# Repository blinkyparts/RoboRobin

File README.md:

# Robo Robin

- A very simple kit for children aged 4 and over
- Plug-in components for easier soldering
- Circuit visible on the back for explanation
- Compatibility of hands with certain other toys of Danish design

- Status: **Complete**
- Difficulty: **1/5**

### Parts List

| Description                   | Quantity |
|-------------------------------|----------|
| RGB LEDs 5mm                  |     2    |
| Button (SMD)                  |     1    |
| CR2032 Battery Holder (THT)   |     1    |
| CR2032 Battery (not included) |     1    |

### Manual
You can find the manual and pictures of every step here: https://github.com/Binary-Kitchen/SolderingTutorial

### 3D Print
There is also a special clamp brick for Robo robin to use in your constructions and imagination.: https://www.printables.com/de/model/513639-klemmbaustein-brick-stand-for-the-robo-robin

### Copyright and Authorship

- Board: [CC-BY-NC-SA 4.0](https://creativecommons.org/licenses/by-nc-sa/4.0/) - [Timo from blinkyparts.com](https://shop.blinkyparts.com)
- Robot SVG [CC-BY-SA 3.0](https://creativecommons.org/licenses/by-sa/3.0/) - [Robot by iconcheese from thenounproject.com](https://thenounproject.com/icon/robot-1159392/) (We bought a licence, you should also honour the author.)

### Buy Soldering Kits
If you want to buy the parts and PCB for a soldering kit you can find everything here: [shop.blinkyparts.com](https://shop.blinkyparts.com/de/Robo-Robin-Loetbausatz-Der-sehr-einfache-lustig-rote-Roboterbausatz/blink239442)

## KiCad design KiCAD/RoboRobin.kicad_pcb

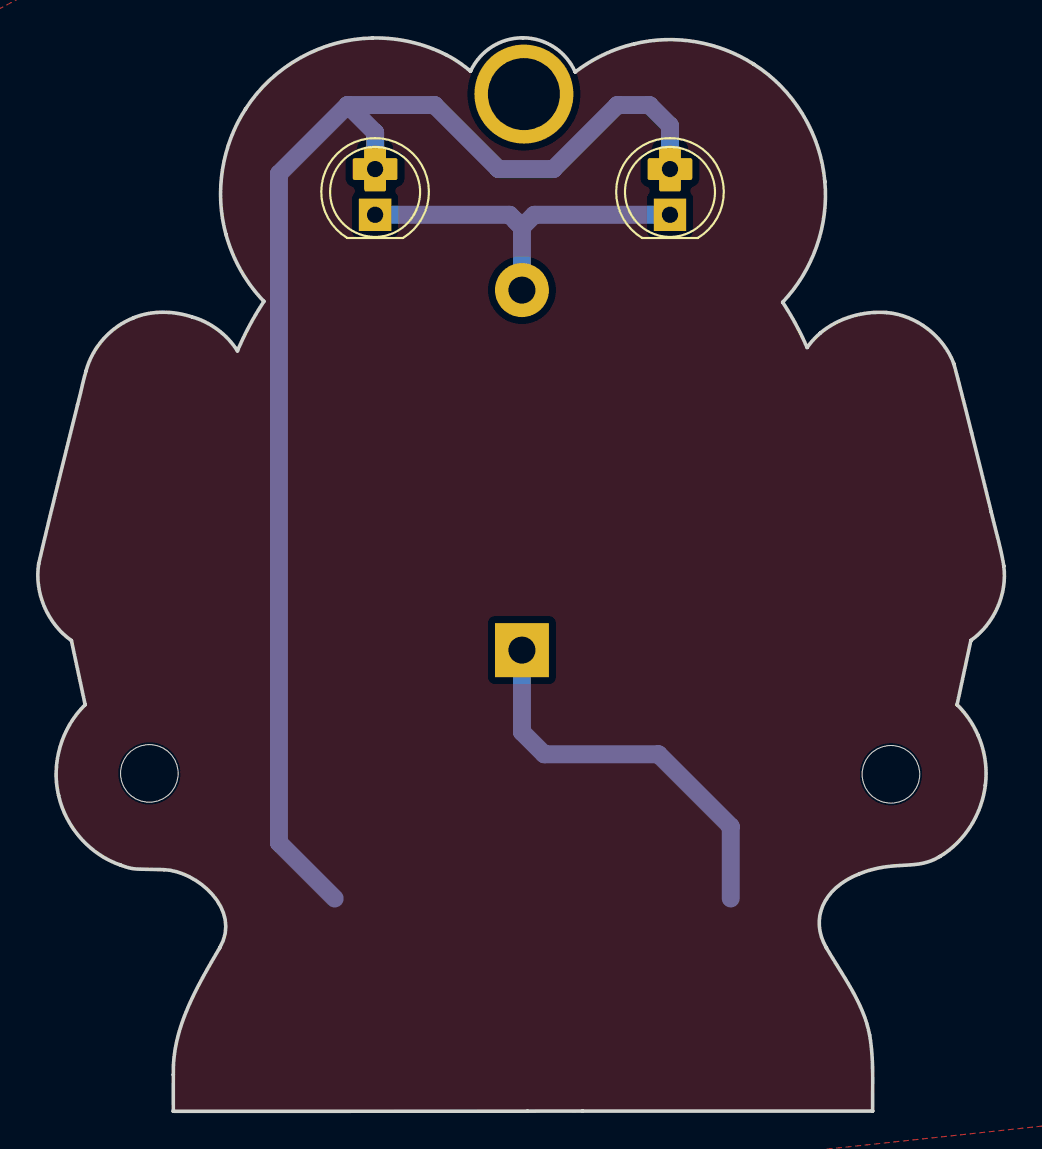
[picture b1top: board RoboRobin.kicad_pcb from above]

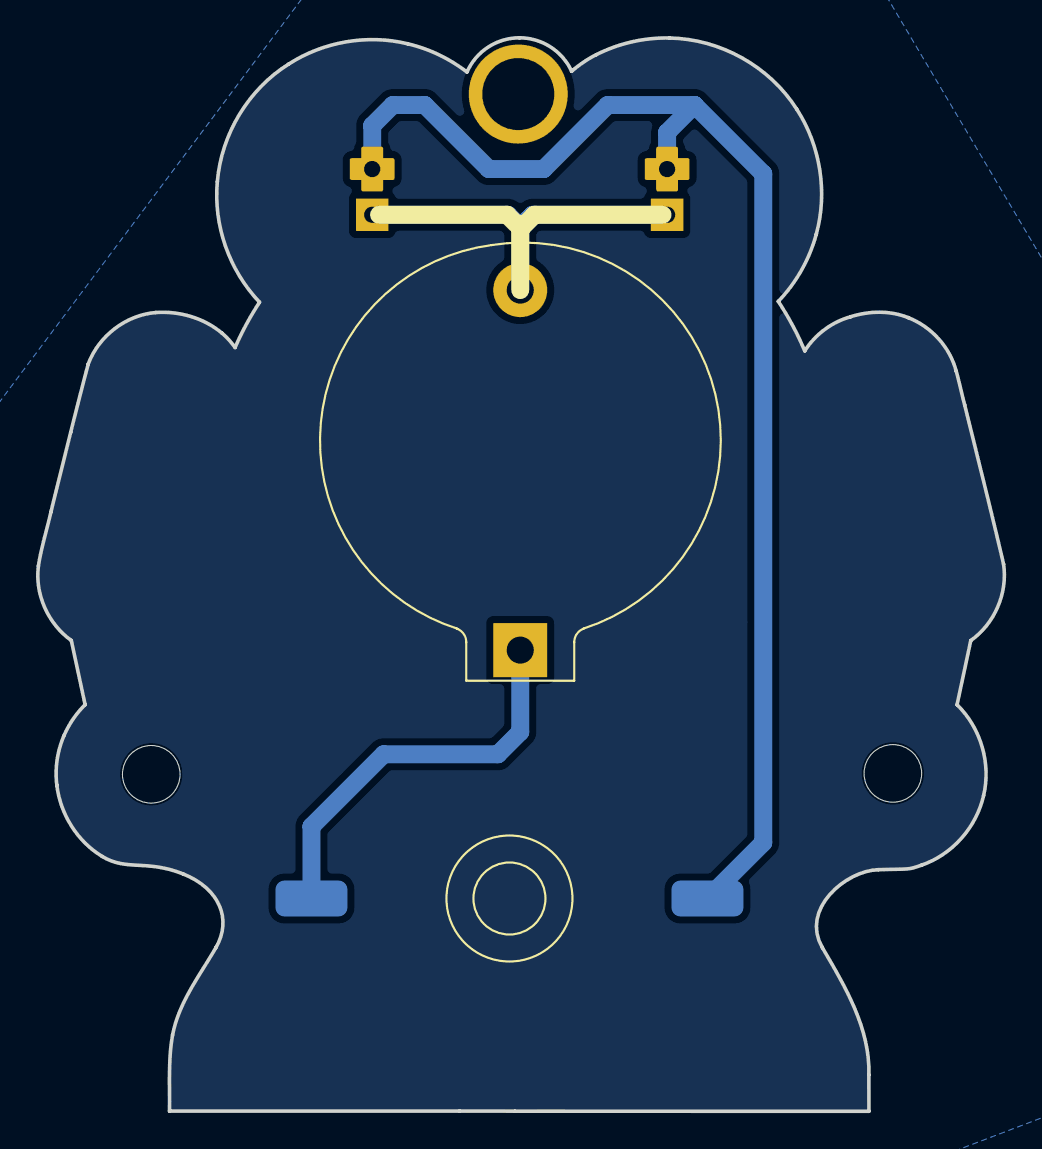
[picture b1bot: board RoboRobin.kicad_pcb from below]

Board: 2 copper layers, 53.7 x 59.6 mm, 8 parts (5 on the bottom side), 3 nets.

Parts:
Batterie: Battery_Cell; BatteryHolder_CR2032_schwarz
D1, D2: LED; LED_D5.0mm_PLUS-Symbol
Ref**: Val**; robi
SW1: SW_DIP_x01; Push_Button
blinkyparts_logo_10mm: G***; logo_blinkyparts_10mm_F.Mask
ce-symbol_mask_3mm: G***; legislation_ce-icon_3mm_F.Mask
weee-symbol_mask_3mm: G***; legislation_weee-icon_3mm_F.Mask

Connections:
+3V0: Batterie.1 (+), SW1.2
GND: Batterie.2 (-), D1.1 (K), D2.1 (K)
VCC: D1.2 (A), D2.2 (A), SW1.1

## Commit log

2026-04-21 updated repository and some maintanance. Created v1.5
2026-04-21 bugfix
2026-04-21 added github specific readme
2026-04-21 fixed image bug
